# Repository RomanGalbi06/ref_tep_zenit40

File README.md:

# Zadanie zo 40. ročníku súťaže ZENIT.
Schémy a dosky plošných spojov si môžeš prezrieť priamo v internetovom prehliadači pomocou [KiCanvas](https://kicanvas.org/):

* **Display modul:** 
  * [Schéma (Schematic)](https://kicanvas.org/?github=https://github.com/RomanGalbi06/ref_tep_zenit40/blob/master/display/display.kicad_sch)
  * [Plošný spoj (PCB)](https://kicanvas.org/?github=https://github.com/RomanGalbi06/ref_tep_zenit40/blob/master/display/display.kicad_pcb)

* **Hardware v1.0:** 
  * [Schéma (Schematic)](https://kicanvas.org/?github=https://github.com/RomanGalbi06/ref_tep_zenit40/blob/master/hardware_v1.0/hardware_v1.0.kicad_sch)
  * [Plošný spoj (PCB)](https://kicanvas.org/?github=https://github.com/RomanGalbi06/ref_tep_zenit40/blob/master/hardware_v1.0/hardware_v1.0.kicad_pcb)

* **Hardware v2.0:** 
  * [Schéma (Schematic)](https://kicanvas.org/?github=https://github.com/RomanGalbi06/ref_tep_zenit40/blob/master/hardware_v2.0/hardware_v2.0.kicad_sch)
  * [Plošný spoj (PCB)](https://kicanvas.org/?github=https://github.com/RomanGalbi06/ref_tep_zenit40/blob/master/hardware_v2.0/hardware_v2.0.kicad_pcb)

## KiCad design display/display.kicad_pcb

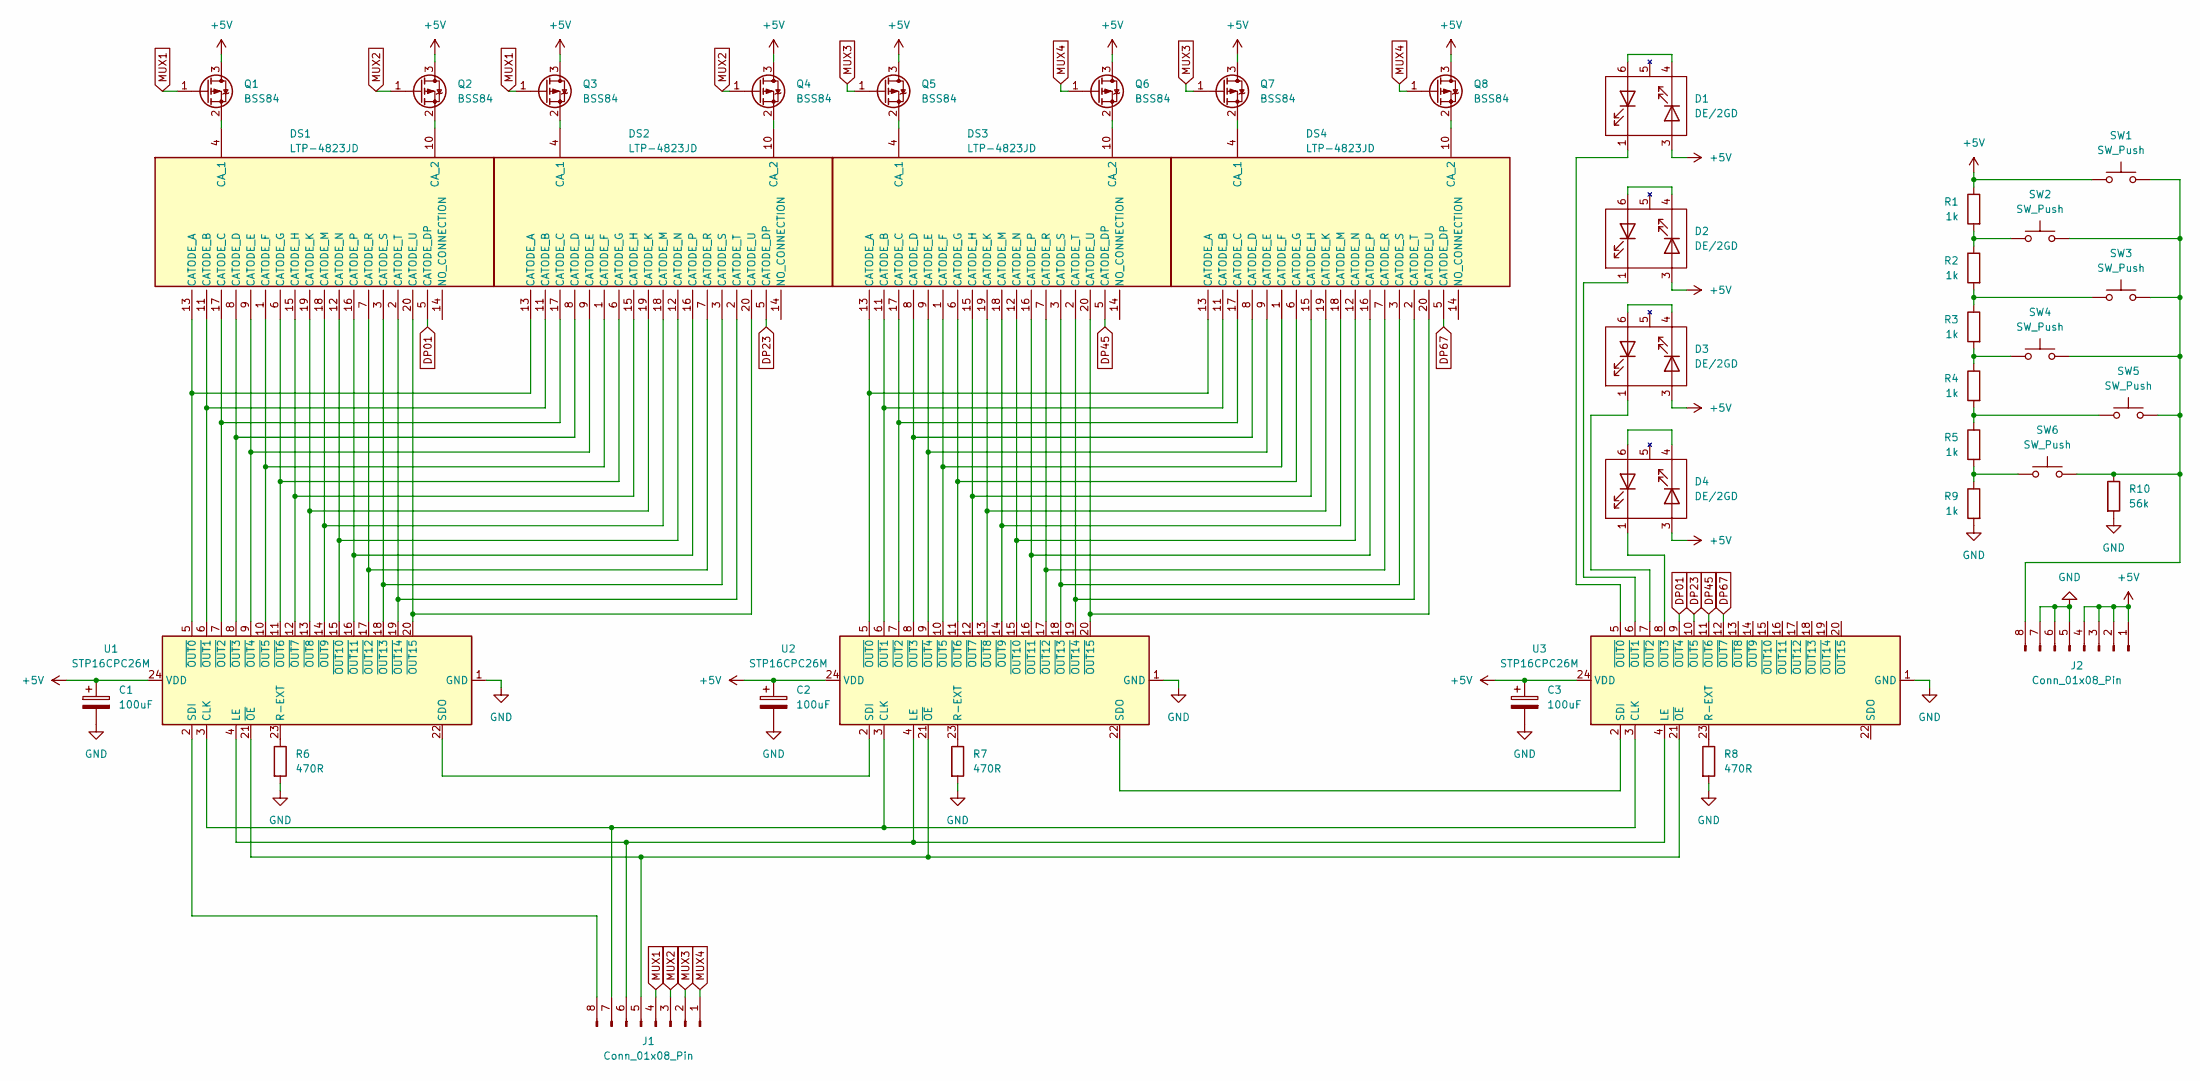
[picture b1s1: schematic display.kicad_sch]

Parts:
C1, C2, C3: 100uF; CP_EIA-6032-15_Kemet-U
D1, D2, D3, D4: DE/2GD; DE_2GD
DS1, DS2, DS3, DS4: LTP-4823JD; Manufacturer_Part_Number LTP-4823JD
J1, J2: Conn_01x08_Pin; PinSocket_1x08_P2.54mm_Vertical
Q1, Q2, Q3, Q4, Q5, Q6, Q7, Q8: BSS84; SOT-23_Handsoldering
R1, R2, R3, R4, R5, R9: 1k; R_1206_3216Metric_Pad1.30x1.75mm_HandSolder
R6, R7, R8: 470R; R_1206_3216Metric_Pad1.30x1.75mm_HandSolder
R10: 56k; R_1206_3216Metric_Pad1.30x1.75mm_HandSolder
SW1, SW2, SW3, SW4, SW5, SW6: SW_Push; SW_Push_1P1T_NO_CK_KSC6xxG
U1, U2, U3: STP16CPC26M; SOIC-24W_7.5x15.4mm_P1.27mm

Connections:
+5V: C1.1, C2.1, C3.1, D1.3, D2.3, D3.3, D4.3, J2.1, J2.2, J2.3, J2.4, Q1.3 (D), Q2.3 (D), Q3.3 (D), Q4.3 (D), Q5.3 (D), Q6.3 (D), Q7.3 (D), Q8.3 (D), R1.1, SW1.1, U1.24 (VDD), U2.24 (VDD), U3.24 (VDD)
DP01: DS1.5 (CATODE_DP), U3.9 (~OUT4)
DP23: DS2.5 (CATODE_DP), U3.10 (~OUT5)
DP45: DS3.5 (CATODE_DP), U3.11 (~OUT6)
DP67: DS4.5 (CATODE_DP), U3.12 (~OUT7)
GND: C1.2, C2.2, C3.2, J2.5, J2.6, J2.7, R6.2, R7.2, R8.2, R9.2, R10.2, U1.1 (GND), U2.1 (GND), U3.1 (GND)
MUX1: J1.4, Q1.1 (G), Q3.1 (G)
MUX2: J1.3, Q2.1 (G), Q4.1 (G)
MUX3: J1.2, Q5.1 (G), Q7.1 (G)
MUX4: J1.1, Q6.1 (G), Q8.1 (G)
unnamed: D1.4, D1.6
unnamed: D2.4, D2.6
unnamed: D3.4, D3.6
unnamed: D4.4, D4.6
unnamed: DS1.13 (CATODE_A), DS2.13 (CATODE_A), U1.5 (~OUT0)
unnamed: DS1.11 (CATODE_B), DS2.11 (CATODE_B), U1.6 (~OUT1)
unnamed: DS1.17 (CATODE_C), DS2.17 (CATODE_C), U1.7 (~OUT2)
unnamed: DS1.8 (CATODE_D), DS2.8 (CATODE_D), U1.8 (~OUT3)
unnamed: DS1.9 (CATODE_E), DS2.9 (CATODE_E), U1.9 (~OUT4)
unnamed: DS1.1 (CATODE_F), DS2.1 (CATODE_F), U1.10 (~OUT5)
unnamed: DS1.6 (CATODE_G), DS2.6 (CATODE_G), U1.11 (~OUT6)
unnamed: DS1.15 (CATODE_H), DS2.15 (CATODE_H), U1.12 (~OUT7)
unnamed: DS1.19 (CATODE_K), DS2.19 (CATODE_K), U1.13 (~OUT8)
unnamed: DS1.18 (CATODE_M), DS2.18 (CATODE_M), U1.14 (~OUT9)
unnamed: DS1.12 (CATODE_N), DS2.12 (CATODE_N), U1.15 (~OUT10)
unnamed: DS1.16 (CATODE_P), DS2.16 (CATODE_P), U1.16 (~OUT11)
unnamed: DS1.7 (CATODE_R), DS2.7 (CATODE_R), U1.17 (~OUT12)
unnamed: DS1.3 (CATODE_S), DS2.3 (CATODE_S), U1.18 (~OUT13)
unnamed: DS1.2 (CATODE_T), DS2.2 (CATODE_T), U1.19 (~OUT14)
unnamed: DS1.20 (CATODE_U), DS2.20 (CATODE_U), U1.20 (~OUT15)
unnamed: DS1.4 (CA_1), Q1.2 (S)
unnamed: DS1.10 (CA_2), Q2.2 (S)
unnamed: DS2.4 (CA_1), Q3.2 (S)
unnamed: DS2.10 (CA_2), Q4.2 (S)
unnamed: DS3.13 (CATODE_A), DS4.13 (CATODE_A), U2.5 (~OUT0)
unnamed: DS3.11 (CATODE_B), DS4.11 (CATODE_B), U2.6 (~OUT1)
unnamed: DS3.17 (CATODE_C), DS4.17 (CATODE_C), U2.7 (~OUT2)
unnamed: DS3.8 (CATODE_D), DS4.8 (CATODE_D), U2.8 (~OUT3)
unnamed: DS3.9 (CATODE_E), DS4.9 (CATODE_E), U2.9 (~OUT4)
unnamed: DS3.1 (CATODE_F), DS4.1 (CATODE_F), U2.10 (~OUT5)
unnamed: DS3.6 (CATODE_G), DS4.6 (CATODE_G), U2.11 (~OUT6)
unnamed: DS3.15 (CATODE_H), DS4.15 (CATODE_H), U2.12 (~OUT7)
unnamed: DS3.19 (CATODE_K), DS4.19 (CATODE_K), U2.13 (~OUT8)
unnamed: DS3.18 (CATODE_M), DS4.18 (CATODE_M), U2.14 (~OUT9)
unnamed: DS3.12 (CATODE_N), DS4.12 (CATODE_N), U2.15 (~OUT10)
unnamed: DS3.16 (CATODE_P), DS4.16 (CATODE_P), U2.16 (~OUT11)
unnamed: DS3.7 (CATODE_R), DS4.7 (CATODE_R), U2.17 (~OUT12)
unnamed: DS3.3 (CATODE_S), DS4.3 (CATODE_S), U2.18 (~OUT13)
unnamed: DS3.2 (CATODE_T), DS4.2 (CATODE_T), U2.19 (~OUT14)
unnamed: DS3.20 (CATODE_U), DS4.20 (CATODE_U), U2.20 (~OUT15)
unnamed: DS3.4 (CA_1), Q5.2 (S)
unnamed: DS3.10 (CA_2), Q6.2 (S)
unnamed: DS4.4 (CA_1), Q7.2 (S)
unnamed: DS4.10 (CA_2), Q8.2 (S)
unnamed: J1.5, U1.21 (~OE), U2.21 (~OE), U3.21 (~OE)
unnamed: J1.6, U1.4 (LE), U2.4 (LE), U3.4 (LE)
unnamed: J1.7, U1.3 (CLK), U2.3 (CLK), U3.3 (CLK)
unnamed: J1.8, U1.2 (SDI)
unnamed: J2.8, R10.1, SW1.2, SW2.2, SW3.2, SW4.2, SW5.2, SW6.2
unnamed: R1.2, R2.1, SW2.1
unnamed: R2.2, R3.1, SW3.1
unnamed: R3.2, R4.1, SW4.1
unnamed: R4.2, R5.1, SW5.1
unnamed: R5.2, R9.1, SW6.1
unnamed: R6.1, U1.23 (R-EXT)
unnamed: U1.22 (SDO), U2.2 (SDI)
unnamed: R7.1, U2.23 (R-EXT)
unnamed: U2.22 (SDO), U3.2 (SDI)
unnamed: R8.1, U3.23 (R-EXT)
unnamed: D1.1, U3.5 (~OUT0)
unnamed: D2.1, U3.6 (~OUT1)
unnamed: D3.1, U3.7 (~OUT2)
unnamed: D4.1, U3.8 (~OUT3)

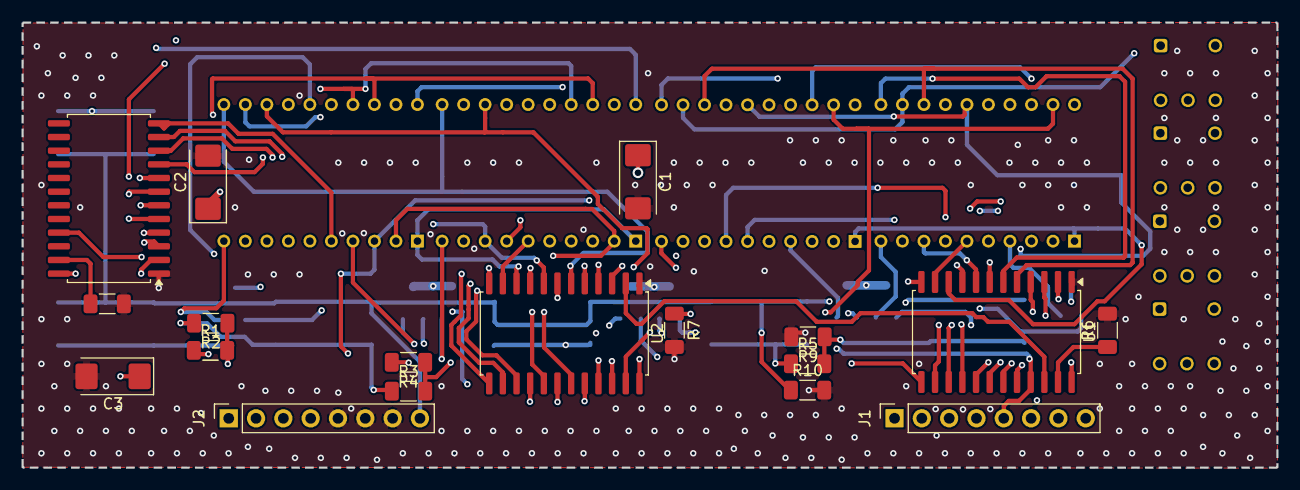
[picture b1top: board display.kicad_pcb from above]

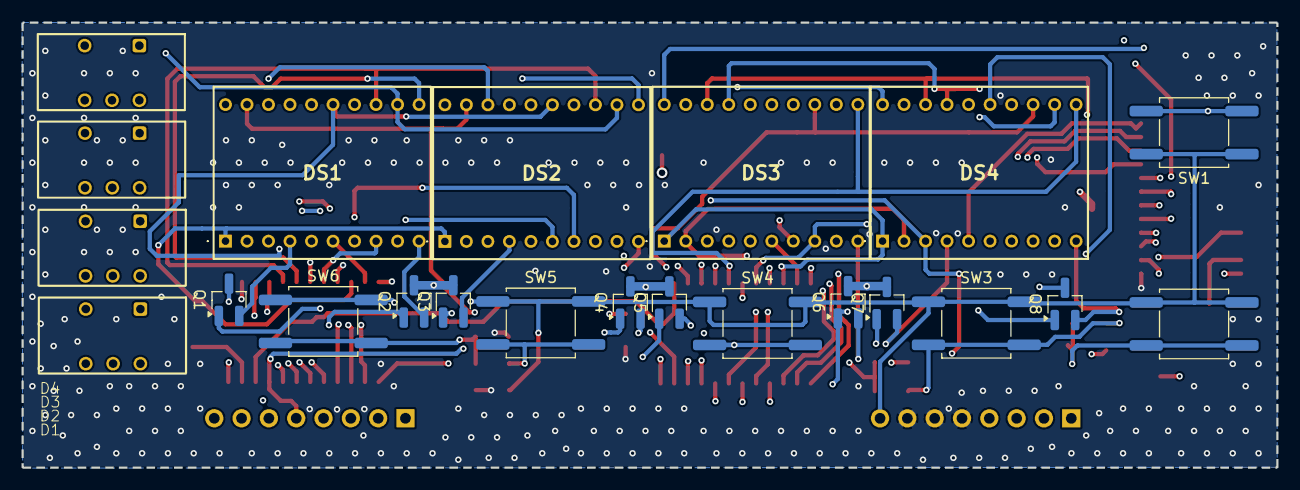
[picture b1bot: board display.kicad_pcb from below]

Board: 4 copper layers, 116.7 x 41.4 mm, 40 parts (22 on the bottom side), 73 nets.

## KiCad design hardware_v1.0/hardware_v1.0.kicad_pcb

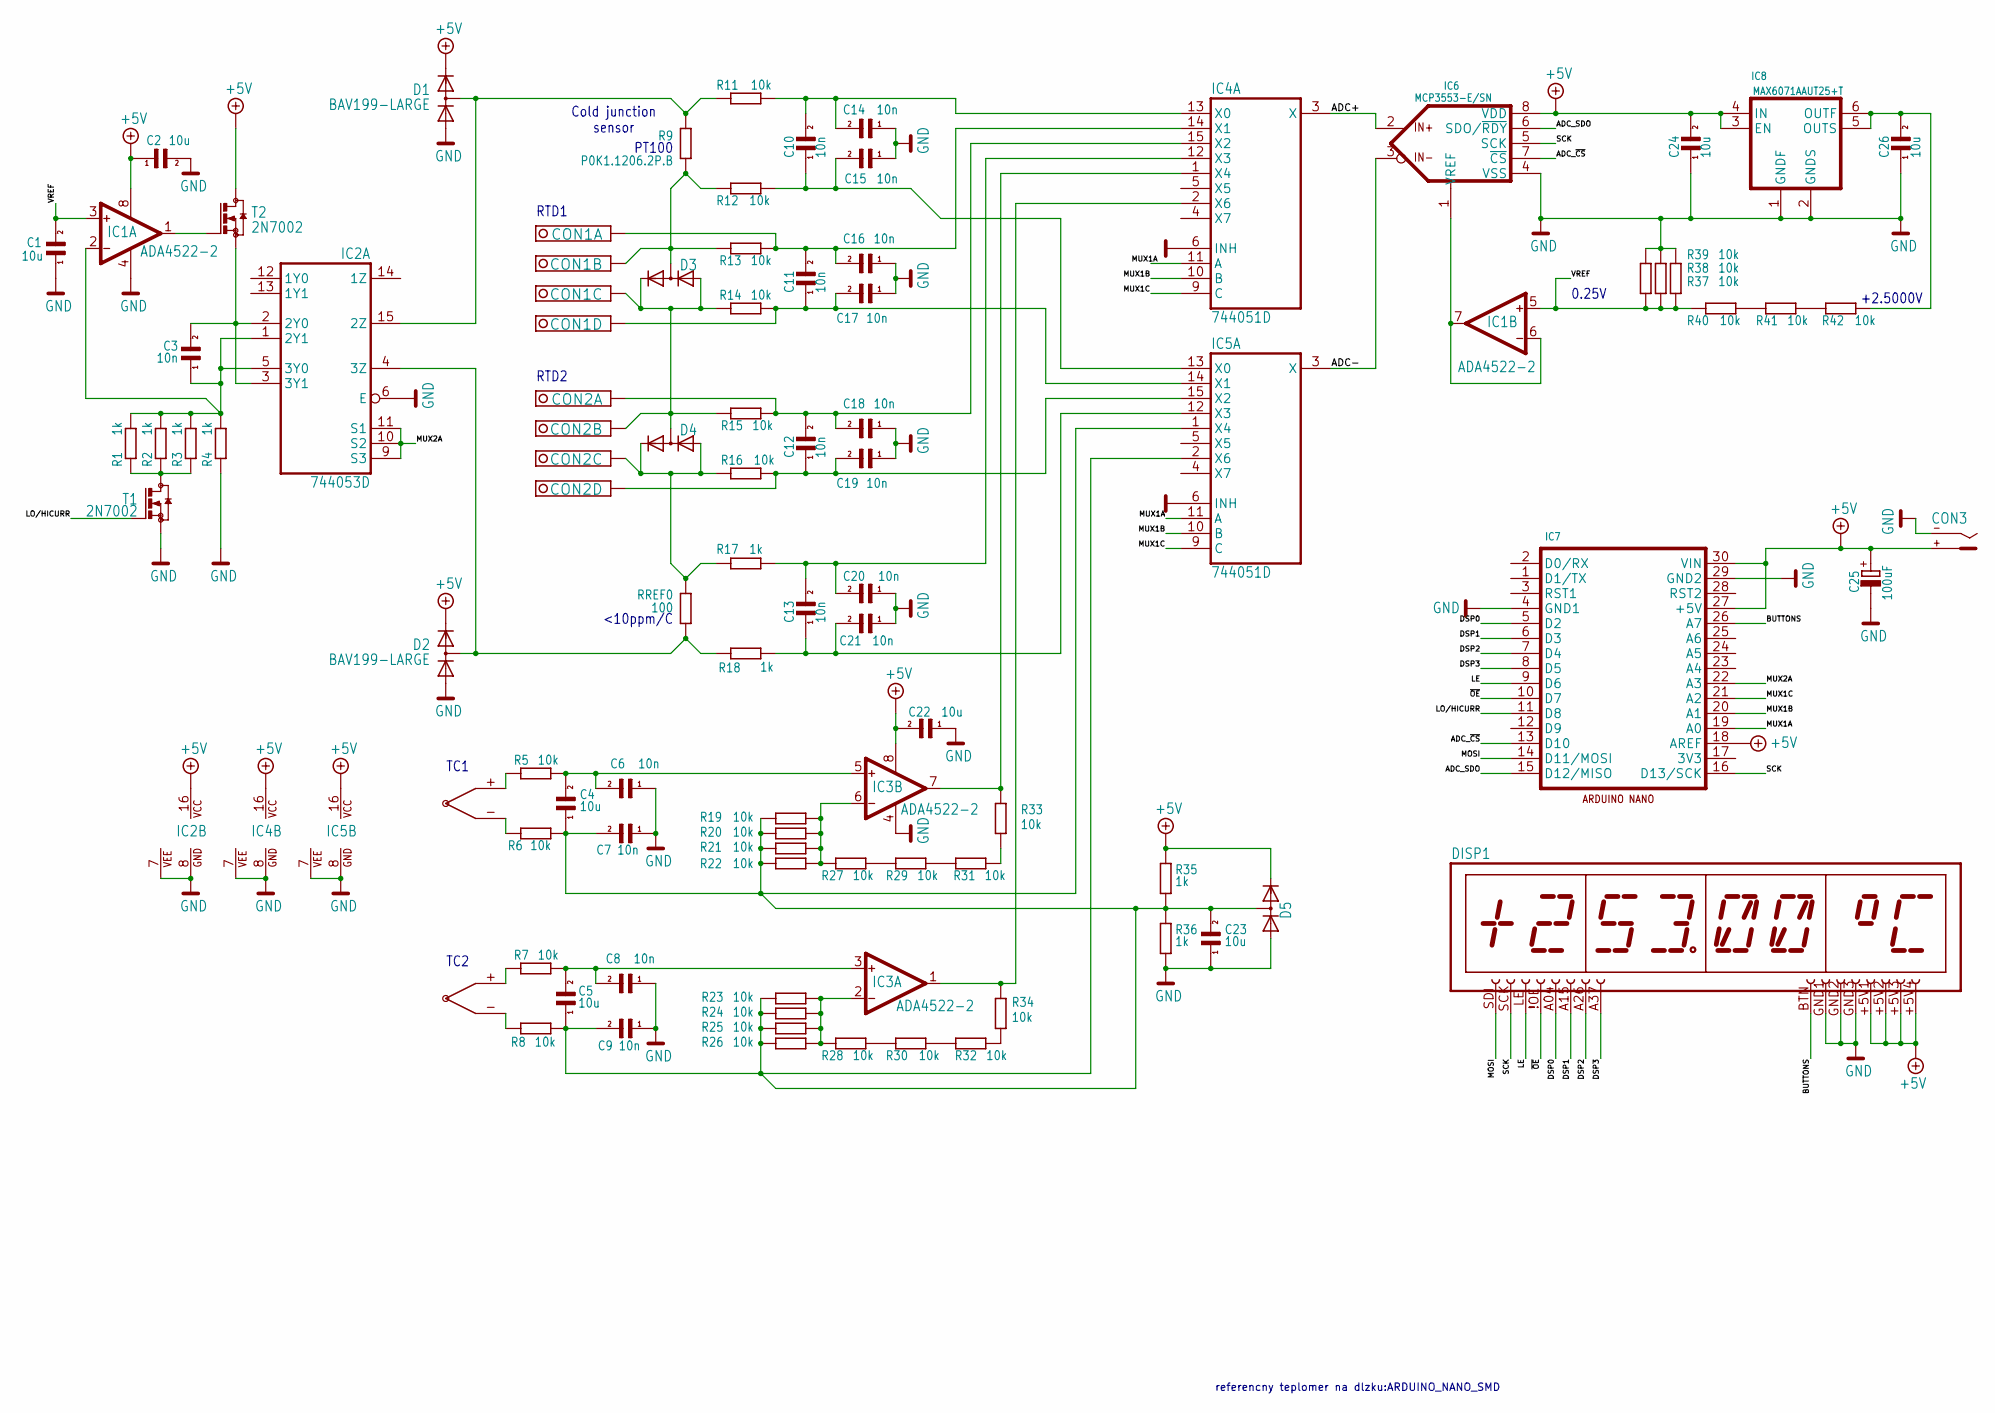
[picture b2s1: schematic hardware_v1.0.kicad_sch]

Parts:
C1, C2, C4, C5, C22, C23, C24, C26: 10u; 1206
C3, C6, C7, C8, C9, C10, C11, C12, C13, C14, C15, C16, C17, C18, C19, C20, C21: 10n; 1206
C25: 100uF; TANTAL_D
CON1, CON2: OQ0412510000G+15EDGK-3.5/4P; OQ0412510000G_THICK
CON3: C9743-CCRNB001R; 2.1MM_2PINS
D1, D2, D3, D4, D5: BAV199-LARGE; SOT23_LARGE
DISP1: DISPLEJHARWIN; DISPLEJ_HARWIN_CONNECTORS
IC1, IC3: ADA4522-2; SO8
IC2: 744053D; SO16
IC4, IC5: 744051D; SO16
IC6: MCP3553-E/SN; SO8
IC7: ARDUINO_NANO-SMD; Arduino_Nano
IC8: MAX6071AAUT25+T; SOT23-6LARGE
R1, R2, R3, R4, R17, R18, R35, R36: 1k; 1206
R5, R6, R7, R8, R11, R12, R13, R14, R15, R16, R19, R20, R21, R22, R23, R24, R25, R26, R27, R28, R29, R30, R31, R32, R33, R34, R37, R38, R39, R40, R41, R42: 10k; 1206
R9: P0K1.1206.2P.B; 1206
RREF0: 100; 1206
T1, T2: 2N7002; SOT23_LARGE
TC1, TC2: IM-K-PCB; AM-K-PCB

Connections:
+5V: C2.1, C22.2, C24.2, C25.+, CON3.1 (+), D1.2 (C), D2.2 (C), D5.2 (C), DISP1.+5V1, DISP1.+5V2, DISP1.+5V3, DISP1.+5V4, IC1.8 (V+), IC2.16 (VCC), IC3.8 (V+), IC4.16 (VCC), IC5.16 (VCC), IC6.8 (VDD), IC7.18 (AREF), IC7.27 (+5V), IC7.30 (VIN), IC8.3 (EN), IC8.4 (IN), R35.2, T2.3 (D)
/ADC+: IC4.3 (X), IC6.2 (VIN+)
/ADC-: IC5.3 (X), IC6.3 (VIN-)
/ADC_SDO: IC6.6 (SDO/~RDY), IC7.15 (D12/MISO)
/ADC_~CS: IC6.7 (~CS), IC7.13 (D10)
/BUTTONS: DISP1.BTN, IC7.26 (A7)
/DSP0: DISP1.A04, IC7.5 (D2)
/DSP1: DISP1.A15, IC7.6 (D3)
/DSP2: DISP1.A26, IC7.7 (D4)
/DSP3: DISP1.A37, IC7.8 (D5)
/LE: DISP1.LE, IC7.9 (D6)
/LO/HICURR: IC7.11 (D8), T1.1 (G)
/MOSI: DISP1.SDI, IC7.14 (D11/MOSI)
/MUX1A: IC4.11 (A), IC5.11 (A), IC7.19 (A0)
/MUX1B: IC4.10 (B), IC5.10 (B), IC7.20 (A1)
/MUX1C: IC4.9 (C), IC5.9 (C), IC7.21 (A2)
/MUX2A: IC2.9 (S3), IC2.10 (S2), IC2.11 (S1), IC7.22 (A3)
/SCK: DISP1.SCK, IC6.5 (SCK), IC7.16 (D13/SCK)
/VREF: C1.2, IC1.3 (IN+), IC1.5 (IN+), R37.2, R38.2, R39.2, R40.1
/~OE: DISP1.!OE (~OE), IC7.10 (D7)
GND: C1.1, C2.2, C6.1, C7.1, C8.1, C9.1, C14.1, C15.1, C16.1, C17.1, C18.1, C19.1, C20.1, C21.1, C22.1, C23.1, C24.1, C25.-, C26.1, CON3.2 (-), D1.1 (A), D2.1 (A), D5.1 (A), DISP1.GND1, DISP1.GND2, DISP1.GND3, IC1.4 (V-), IC2.6 (E), IC2.7 (VEE), IC2.8 (GND), IC3.4 (V-), IC4.6 (INH), IC4.7 (VEE), IC4.8 (GND), IC5.6 (INH), IC5.7 (VEE), IC5.8 (GND), IC6.4 (VSS), IC7.4 (GND1), IC7.29 (GND2), IC8.1 (GNDF), IC8.2 (GNDS), R4.1, R36.1, R37.1, R38.1, R39.1, T1.2 (S)
unnamed: C11.2, C16.2, CON1.1 (K), IC4.14 (X1), R13.2
unnamed: CON1.2 (K), D3.3 (AC), R9.1, R12.1, R13.1
unnamed: CON1.3 (K), CON2.2 (K), D3.1 (A), D3.2 (C), D4.3 (AC), R14.1, R15.1
unnamed: C11.1, C17.2, CON1.4 (K), IC5.14 (X1), R14.2
unnamed: C12.2, C18.2, CON2.1 (K), IC4.15 (X2), R15.2
unnamed: CON2.3 (K), D4.1 (A), D4.2 (C), R16.1, R17.1, RREF0.2
unnamed: C12.1, C19.2, CON2.4 (K), IC5.15 (X2), R16.2
unnamed: D1.3 (AC), IC2.15 (2Z), R9.2, R11.1
unnamed: D2.3 (AC), IC2.4 (3Z), R18.1, RREF0.1
unnamed: C4.1, C5.1, C7.2, C9.2, C23.2, D5.3 (AC), IC5.1 (X4), IC5.2 (X6), R6.2, R8.2, R19.1, R20.1, R21.1, R22.1, R23.1, R24.1, R25.1, R26.1, R35.1, R36.2
unnamed: C3.1, IC1.2 (IN-), IC2.1 (2Y1), IC2.5 (3Y0), R1.2, R2.2, R3.2, R4.2
unnamed: IC1.1 (OUT), T2.1 (G)
unnamed: IC1.6 (IN-), IC1.7 (OUT), IC6.1 (VREF)
unnamed: C3.2, IC2.2 (2Y0), IC2.3 (3Y1), T2.2 (S)
unnamed: C5.2, C8.2, IC3.3 (IN+), R7.2
unnamed: IC3.2 (IN-), R23.2, R24.2, R25.2, R26.2, R28.1
unnamed: IC3.1 (OUT), IC4.2 (X6), R34.2
unnamed: C4.2, C6.2, IC3.5 (IN+), R5.2
unnamed: IC3.6 (IN-), R19.2, R20.2, R21.2, R22.2, R27.1
unnamed: IC3.7 (OUT), IC4.1 (X4), R33.2
unnamed: C10.2, C14.2, IC4.13 (X0), R11.2
unnamed: C13.2, C20.2, IC4.12 (X3), R17.2
unnamed: C10.1, C15.2, IC5.13 (X0), R12.2
unnamed: C13.1, C21.2, IC5.12 (X3), R18.2
unnamed: C26.2, IC8.5 (OUTS), IC8.6 (OUTF), R42.2
unnamed: R5.1, TC1.+
unnamed: R6.1, TC1.-
unnamed: R7.1, TC2.+
unnamed: R8.1, TC2.-
unnamed: R27.2, R29.1
unnamed: R28.2, R30.1
unnamed: R29.2, R31.1
unnamed: R30.2, R32.1
unnamed: R31.2, R33.1
unnamed: R32.2, R34.1
unnamed: R40.2, R41.1
unnamed: R41.2, R42.1
unnamed: R1.1, R2.1, R3.1, T1.3 (D)

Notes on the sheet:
<10ppm/C
PT100
RTD1
Cold junction sensor
0.25V
RTD2
+2.5000V
referencny teplomer na dlzku:ARDUINO_NANO_SMD
TC1
TC2

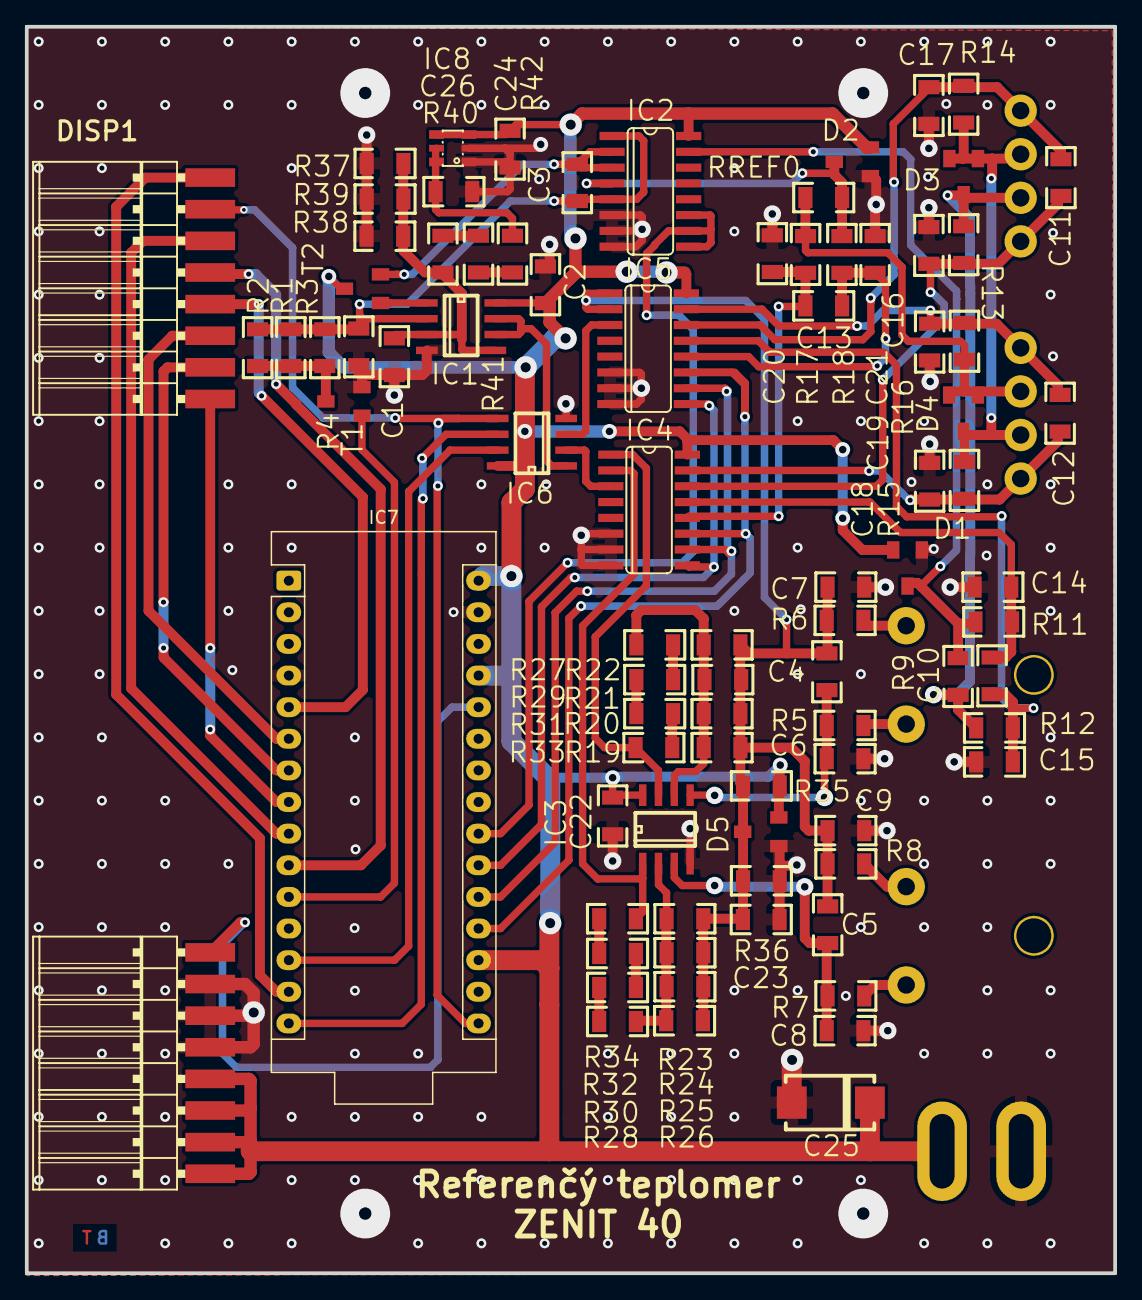
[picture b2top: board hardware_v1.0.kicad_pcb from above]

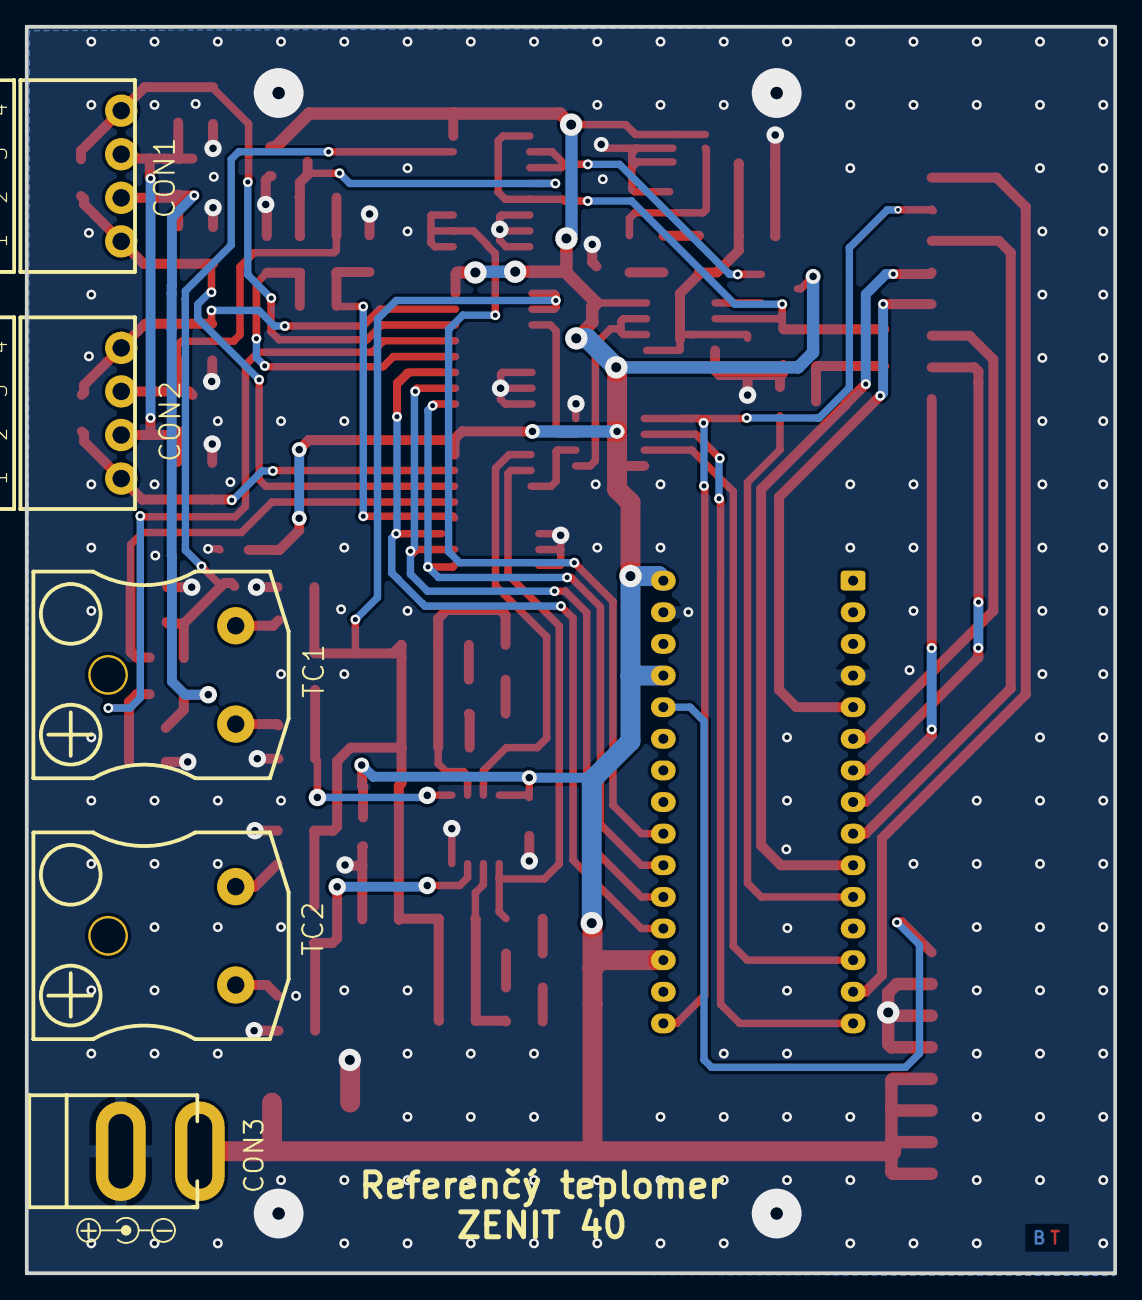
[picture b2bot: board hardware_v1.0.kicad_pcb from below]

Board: 2 copper layers, 87.4 x 100.1 mm, 89 parts (5 on the bottom side), 59 nets.

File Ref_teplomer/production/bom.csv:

Designator,Footprint,Quantity,Value,LCSC Part #
"C1, C2, C22, C23, C24, C26, C4, C5",1206,8,10u,
"C10, C11, C12, C13, C14, C15, C16, C17, C18, C19, C20, C21, C3, C6, C7, C8, C9",1206,17,10n,
C25,TANTAL_D,1,100uF,
"CON1, CON2",OQ0412510000G_THICK,2,OQ0412510000G+15EDGK-3.5/4P,
CON3,2.1MM_2PINS,1,C9743-CCRNB001R,
"D1, D2, D3, D4, D5",SOT23_LARGE,5,BAV199-LARGE,
DISP1,DISPLEJ_HARWIN_CONNECTORS,1,DISPLEJHARWIN,
"IC1, IC3",SO8,2,ADA4522-2,
IC2,SO16,1,744053D,
"IC4, IC5",SO16,2,744051D,
IC6,SO8,1,MCP3553-E/SN,
IC7,Arduino_Nano,1,ARDUINO_NANO-SMD,
IC8,SOT23-6LARGE,1,MAX6071AAUT25+T,
"R1, R17, R18, R2, R3, R35, R36, R4",1206,8,1k,
"R11, R12, R13, R14, R15, R16, R19, R20, R21, R22, R23, R24, R25, R26, R27, R28, R29, R30, R31, R32, R33, R34, R37, R38, R39, R40, R41, R42, R5, R6, R7, R8",1206,32,10k,
R9,1206,1,P0K1.1206.2P.B,
RREF0,1206,1,100,
"T1, T2",SOT23_LARGE,2,2N7002,
"TC1, TC2",AM-K-PCB,2,IM-K-PCB,
